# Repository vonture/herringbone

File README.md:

Herringbone
===============

A split ortholinear grid keyboard made with through hole components.

## Inspired by
 - [Plaid](https://github.com/hsgw/plaid)
 - [Torn](https://github.com/rtitmuss/torn)
 - [Discipline](https://github.com/coseyfannitutti/discipline)

## BOM

https://octopart.com/bom-tool/v2/9F35A43C-BB16-4669-B263-24A030B88F93

## License

The Herringbone Keyboard is licensed under [Creative Commons Attribution-NonCommercial 4.0 International License](https://creativecommons.org/licenses/by-nc/4.0).

This PCB design may be freely reproduced, modified, and manufactured for personal use only.

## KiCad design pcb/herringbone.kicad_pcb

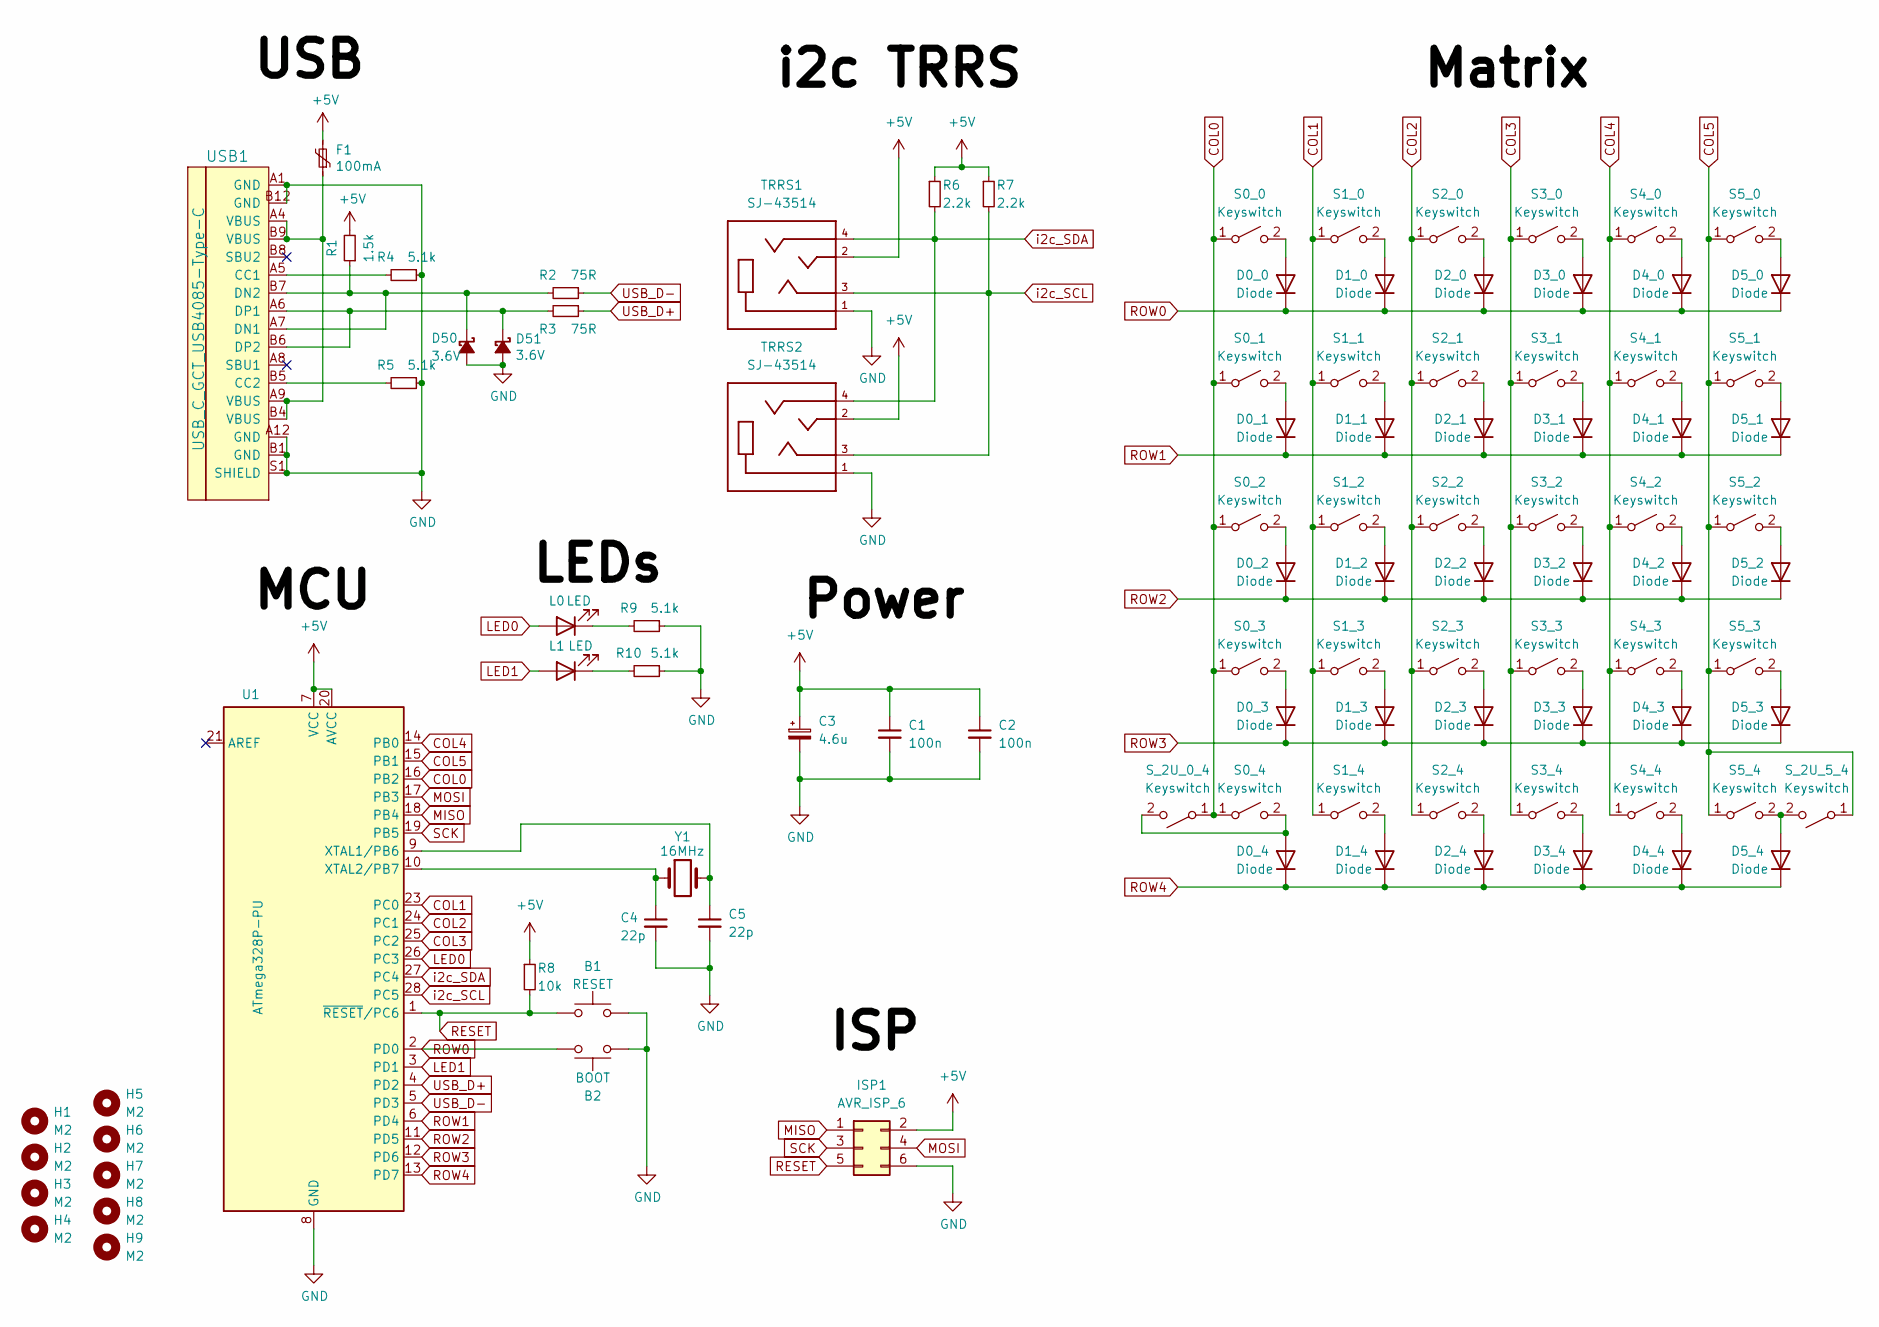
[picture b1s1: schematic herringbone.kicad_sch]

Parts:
B1: RESET; SW_PUSH_6mm
B2: BOOT; SW_PUSH_6mm
C1, C2: 100n; C_Disc_D4.3mm_W1.9mm_P5.00mm
C3: 4.6u; CP_Radial_D4.0mm_P1.50mm
C4, C5: 22p; C_Disc_D4.3mm_W1.9mm_P5.00mm
D0_0, D0_1, D0_2, D0_3, D0_4, D1_0, D1_1, D1_2, D1_3, D1_4, D2_0, D2_1, D2_2, D2_3, D2_4, D3_0, D3_1, D3_2, D3_3, D3_4, D4_0, D4_1, D4_2, D4_3, D4_4, D5_0, D5_1, D5_2, D5_3, D5_4: Diode; D_DO-35_SOD27_P5.08mm_Horizontal
D50, D51: 3.6V; D_DO-35_SOD27_P5.08mm_Horizontal
F1: 100mA; polyfuse_5.1mm
H1, H2, H3, H4, H5, H6, H7, H8, H9: M2; MountingHole_2.2mm_M2_Pad
ISP1: AVR_ISP_6; AVR_ICSP_3x2
L0, L1: LED; LED_D3.0mm
R1: 1.5k; R_Axial_DIN0204_L3.6mm_D1.6mm_P5.08mm_Horizontal
R2, R3: 75R; R_Axial_DIN0204_L3.6mm_D1.6mm_P5.08mm_Horizontal
R4, R5, R9, R10: 5.1k; R_Axial_DIN0204_L3.6mm_D1.6mm_P5.08mm_Horizontal
R6, R7: 2.2k; R_Axial_DIN0204_L3.6mm_D1.6mm_P5.08mm_Horizontal
R8: 10k; R_Axial_DIN0204_L3.6mm_D1.6mm_P5.08mm_Horizontal
S0_0, S0_1, S0_2, S0_3, S0_4, S1_0, S1_1, S1_2, S1_3, S1_4, S2_0, S2_1, S2_2, S2_3, S2_4, S3_0, S3_1, S3_2, S3_3, S3_4, S4_0, S4_1, S4_2, S4_3, S4_4, S5_0, S5_1, S5_2, S5_3, S5_4: Keyswitch; SW_Hotswap_Kailh_MX_1.00u
S_2U_0_4, S_2U_5_4: Keyswitch; SW_Hotswap_Kailh_MX_2.00u
TRRS1, TRRS2: SJ-43514; CUI_SJ-43514
U1: ATmega328P-PU; ATMEGA328-PU_DIP-28_W7.62mm_Socket
USB1: USB_C_GCT_USB4085-Type-C; USB_C_GCT_USB4085
Y1: 16MHz; Crystal_HC49-4H_Vertical

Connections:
+5V: C1.1, C2.1, C3.1, F1.2, ISP1.2, R1.2, R6.1, R7.1, R8.1, TRRS1.2, TRRS2.2, U1.7 (VCC), U1.20 (AVCC)
COL0: S0_0.1 (A), S0_1.1 (A), S0_2.1 (A), S0_3.1 (A), S0_4.1 (A), S_2U_0_4.1 (A), U1.16 (PB2)
COL1: S1_0.1 (A), S1_1.1 (A), S1_2.1 (A), S1_3.1 (A), S1_4.1 (A), U1.23 (PC0)
COL2: S2_0.1 (A), S2_1.1 (A), S2_2.1 (A), S2_3.1 (A), S2_4.1 (A), U1.24 (PC1)
COL3: S3_0.1 (A), S3_1.1 (A), S3_2.1 (A), S3_3.1 (A), S3_4.1 (A), U1.25 (PC2)
COL4: S4_0.1 (A), S4_1.1 (A), S4_2.1 (A), S4_3.1 (A), S4_4.1 (A), U1.14 (PB0)
COL5: S5_0.1 (A), S5_1.1 (A), S5_2.1 (A), S5_3.1 (A), S5_4.1 (A), S_2U_5_4.1 (A), U1.15 (PB1)
GND: B1.2, B2.1, C1.2, C2.2, C3.2, C4.2, C5.2, D50.2 (A), D51.2 (A), ISP1.6, R4.1, R5.1, R9.1, R10.1, TRRS1.1, TRRS2.1, U1.8 (GND), U1.22 (GND), USB1.A1 (GND), USB1.A12 (GND), USB1.B1 (GND), USB1.B12 (GND), USB1.S1 (SHIELD)
LED0: L0.2 (A), U1.26 (PC3)
LED1: L1.2 (A), U1.3 (PD1)
MISO: ISP1.1, U1.18 (PB4)
MOSI: ISP1.4, U1.17 (PB3)
unnamed: D0_0.2 (A), S0_0.2 (B)
unnamed: D0_1.2 (A), S0_1.2 (B)
unnamed: D0_2.2 (A), S0_2.2 (B)
unnamed: D0_3.2 (A), S0_3.2 (B)
unnamed: D0_4.2 (A), S0_4.2 (B), S_2U_0_4.2 (B)
unnamed: D1_0.2 (A), S1_0.2 (B)
unnamed: D1_1.2 (A), S1_1.2 (B)
unnamed: D1_2.2 (A), S1_2.2 (B)
unnamed: D1_3.2 (A), S1_3.2 (B)
unnamed: D1_4.2 (A), S1_4.2 (B)
unnamed: D2_0.2 (A), S2_0.2 (B)
unnamed: D2_1.2 (A), S2_1.2 (B)
unnamed: D2_2.2 (A), S2_2.2 (B)
unnamed: D2_3.2 (A), S2_3.2 (B)
unnamed: D2_4.2 (A), S2_4.2 (B)
unnamed: D3_0.2 (A), S3_0.2 (B)
unnamed: D3_1.2 (A), S3_1.2 (B)
unnamed: D3_2.2 (A), S3_2.2 (B)
unnamed: D3_3.2 (A), S3_3.2 (B)
unnamed: D3_4.2 (A), S3_4.2 (B)
unnamed: D4_0.2 (A), S4_0.2 (B)
unnamed: D4_1.2 (A), S4_1.2 (B)
unnamed: D4_2.2 (A), S4_2.2 (B)
unnamed: D4_3.2 (A), S4_3.2 (B)
unnamed: D4_4.2 (A), S4_4.2 (B)
unnamed: D5_0.2 (A), S5_0.2 (B)
unnamed: D5_1.2 (A), S5_1.2 (B)
unnamed: D5_2.2 (A), S5_2.2 (B)
unnamed: D5_3.2 (A), S5_3.2 (B)
unnamed: D5_4.2 (A), S5_4.2 (B), S_2U_5_4.2 (B)
unnamed: D50.1 (K), R1.1, R2.2, USB1.A7 (DN1), USB1.B7 (DN2)
unnamed: D51.1 (K), R3.2, USB1.A6 (DP1), USB1.B6 (DP2)
unnamed: F1.1, USB1.A4 (VBUS), USB1.A9 (VBUS), USB1.B4 (VBUS), USB1.B9 (VBUS)
unnamed: L0.1 (K), R9.2
unnamed: L1.1 (K), R10.2
unnamed: C5.1, U1.9 (XTAL1/PB6), Y1.2
unnamed: C4.1, U1.10 (XTAL2/PB7), Y1.1
unnamed: R4.2, USB1.A5 (CC1)
unnamed: R5.2, USB1.B5 (CC2)
RESET: B1.1, ISP1.5, R8.2, U1.1 (~RESET/PC6)
ROW0: B2.2, D0_0.1 (K), D1_0.1 (K), D2_0.1 (K), D3_0.1 (K), D4_0.1 (K), D5_0.1 (K), U1.2 (PD0)
ROW1: D0_1.1 (K), D1_1.1 (K), D2_1.1 (K), D3_1.1 (K), D4_1.1 (K), D5_1.1 (K), U1.6 (PD4)
ROW2: D0_2.1 (K), D1_2.1 (K), D2_2.1 (K), D3_2.1 (K), D4_2.1 (K), D5_2.1 (K), U1.11 (PD5)
ROW3: D0_3.1 (K), D1_3.1 (K), D2_3.1 (K), D3_3.1 (K), D4_3.1 (K), D5_3.1 (K), U1.12 (PD6)
ROW4: D0_4.1 (K), D1_4.1 (K), D2_4.1 (K), D3_4.1 (K), D4_4.1 (K), D5_4.1 (K), U1.13 (PD7)
SCK: ISP1.3, U1.19 (PB5)
USB_D+: R3.1, U1.4 (PD2)
USB_D-: R2.1, U1.5 (PD3)
i2c_SCL: R7.2, TRRS1.3, TRRS2.3, U1.28 (PC5)
i2c_SDA: R6.2, TRRS1.4, TRRS2.4, U1.27 (PC4)

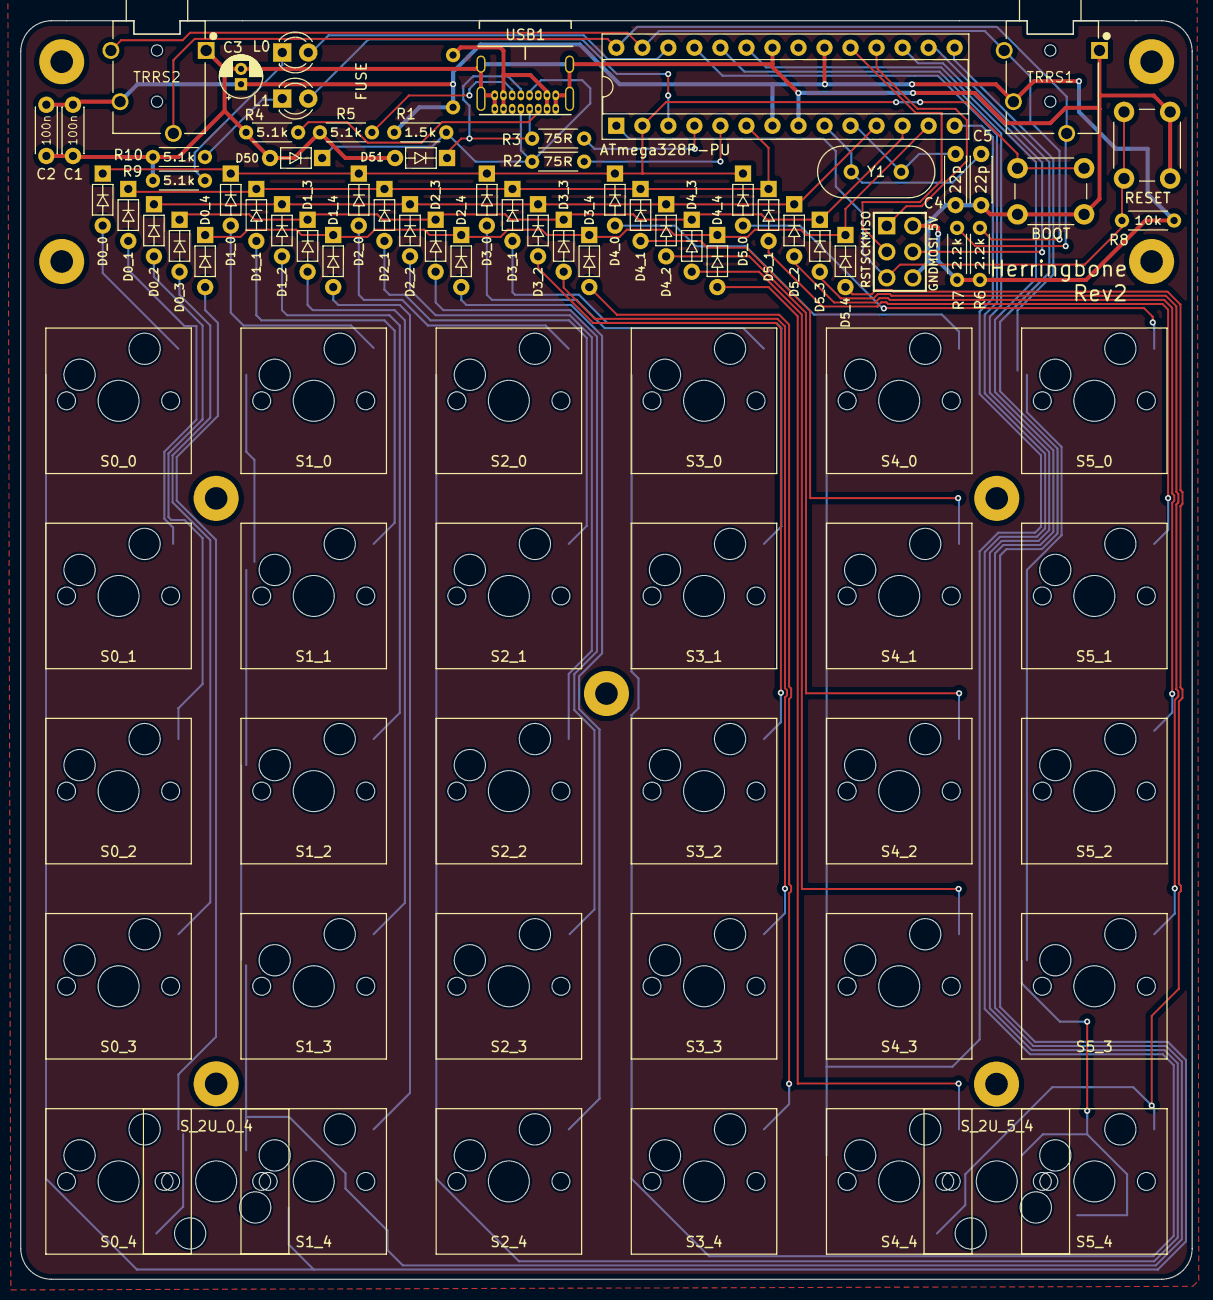
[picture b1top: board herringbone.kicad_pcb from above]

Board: 2 copper layers, 114.3 x 122.8 mm, 99 parts (0 on the bottom side), 62 nets.

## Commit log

2025-03-29 Initial schematics and pcb design.
2025-03-29 Second TRRS jack
2025-03-29 Rebuild zones.
2025-03-29 Cleanups
2025-03-30 Add new footprints and add models.
2025-03-30 Add plate and bottom.
2025-03-31 Acrylic top and bottom.
2025-04-05 Add acrylic cutouts.
2025-04-05 Remove uneeded kidad_pro file
2025-04-05 Readme and license files.
2025-04-05 Move kicad projects to subfolders.
2025-04-05 Images in readme.
2025-04-05 Remove duplicate file.
2025-04-05 Revert "Remove duplicate file."
    This reverts commit 3b0df11ec183bf3265078285f9d428ba2c2dcfc6.
2025-04-12 PCB rev2.
    - Add LEDs
    - Fix D+ D- USB pins for USBaspLoader to be happy
    - Widen power Lines
    - Allow for 2U keys in bottom corners
2025-04-12 Add BOM
2025-04-12 Update image of rev2 pcb.
2025-04-12 Remove dependencies
2025-04-13 Add case models.
2025-04-13 pcb and footprint updates.
2025-04-19 rev2 renderings
2025-04-19 Add image of soldered board.
2025-04-20 Add dep on bootloader.
